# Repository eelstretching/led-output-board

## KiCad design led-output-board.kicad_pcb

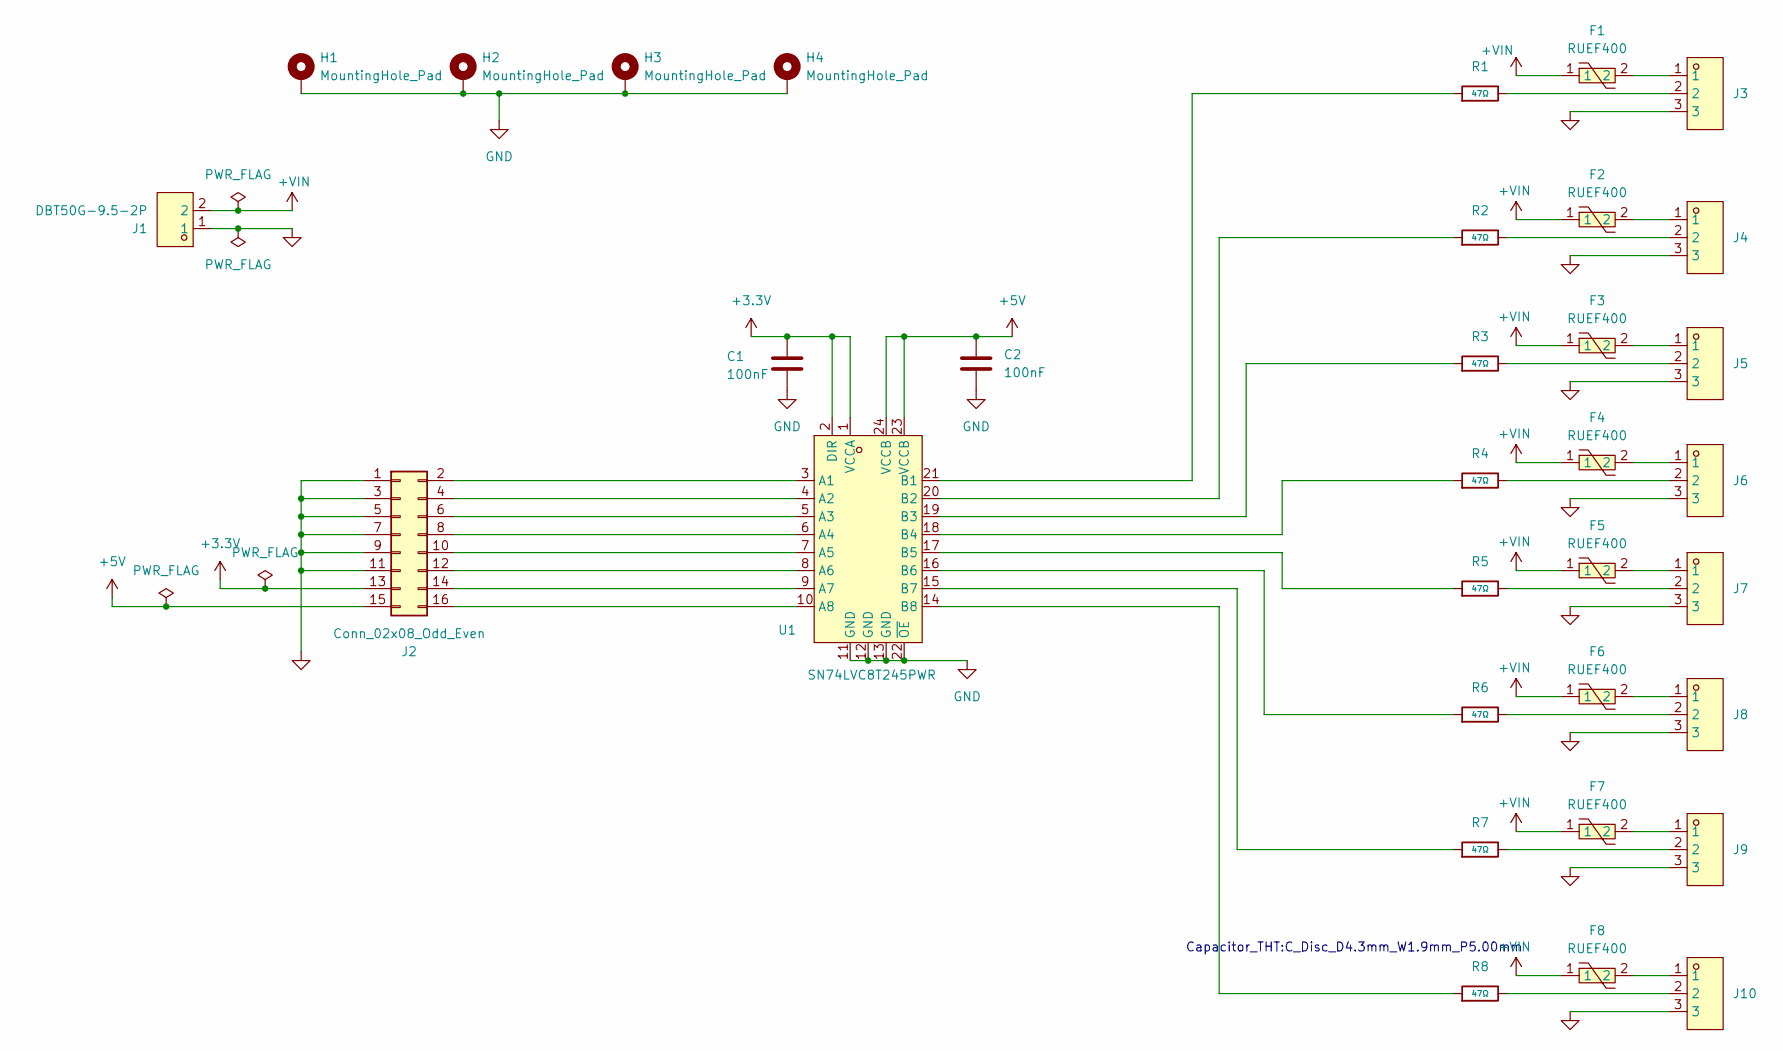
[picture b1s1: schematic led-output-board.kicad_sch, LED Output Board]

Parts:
C1, C2: 100nF; C_Disc_D4.3mm_W1.9mm_P5.00mm
F1, F2, F3, F4, F5, F6, F7, F8: RUEF400; FUSE-TH_L14.0-W3.0-P5.08-D0.6; MPN RUEF400; LCSC Part C2760163
H1, H2, H3, H4: MountingHole_Pad; MountingHole_3.2mm_M3_Pad
J1: DBT50G-9.5-2P; CONN-TH_2P-P9.50_DBT50G-9.5-2P
J2: Conn_02x08_Odd_Even; IDC-Header_2x08_P2.54mm_Vertical
J3, J4, J5, J6, J7, J8, J9, J10: DB301V-3.5-3P-GN; CONN-TH_DB301V-3.5-3P-GN; LCSC Part C695630
R1, R2, R3, R4, R5, R6, R7, R8: 47Ω; R_Axial_DIN0204_L3.6mm_D1.6mm_P2.54mm_Vertical; Overload Voltage (Max) 50V; Tolerance ±1%; Part 0402WGF470JTCE
U1: SN74LVC8T245PWR; TSSOP-24_L7.8-W4.4-P0.65-LS6.4-BL; LCSC Part C27643

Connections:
+3.3V: C1.1, J2.13, U1.1 (VCCA), U1.2 (DIR)
+5V: C2.1, J2.15, U1.23 (VCCB), U1.24 (VCCB)
+VIN: F1.1, F2.1, F3.1, F4.1, F5.1, F6.1, F7.1, F8.1, J1.2
GND: C1.2, C2.2, H1.1 (1_1), H2.1 (1_1), H3.1 (1_1), H4.1 (1_1), J1.1, J2.1, J2.3, J2.5, J2.7, J2.9, J2.11, J3.3, J4.3, J5.3, J6.3, J7.3, J8.3, J9.3, J10.3, U1.11 (GND), U1.12 (GND), U1.13 (GND), U1.22 (~OE)
unnamed: F1.2, J3.1
unnamed: F2.2, J4.1
unnamed: F3.2, J5.1
unnamed: F4.2, J6.1
unnamed: F5.2, J7.1
unnamed: F6.2, J8.1
unnamed: F7.2, J9.1
unnamed: F8.2, J10.1
unnamed: J2.2, U1.3 (A1)
unnamed: J2.4, U1.4 (A2)
unnamed: J2.6, U1.5 (A3)
unnamed: J2.8, U1.6 (A4)
unnamed: J2.10, U1.7 (A5)
unnamed: J2.12, U1.8 (A6)
unnamed: J2.14, U1.9 (A7)
unnamed: J2.16, U1.10 (A8)
unnamed: J3.2, R1.2
unnamed: J4.2, R2.2
unnamed: J5.2, R3.2
unnamed: J6.2, R4.2
unnamed: J7.2, R5.2
unnamed: J8.2, R6.2
unnamed: J9.2, R7.2
unnamed: J10.2, R8.2
unnamed: R1.1, U1.21 (B1)
unnamed: R2.1, U1.20 (B2)
unnamed: R3.1, U1.19 (B3)
unnamed: R4.1, U1.18 (B4)
unnamed: R5.1, U1.17 (B5)
unnamed: R6.1, U1.16 (B6)
unnamed: R7.1, U1.15 (B7)
unnamed: R8.1, U1.14 (B8)

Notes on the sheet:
Capacitor_THT:C_Disc_D4.3mm_W1.9mm_P5.00mm

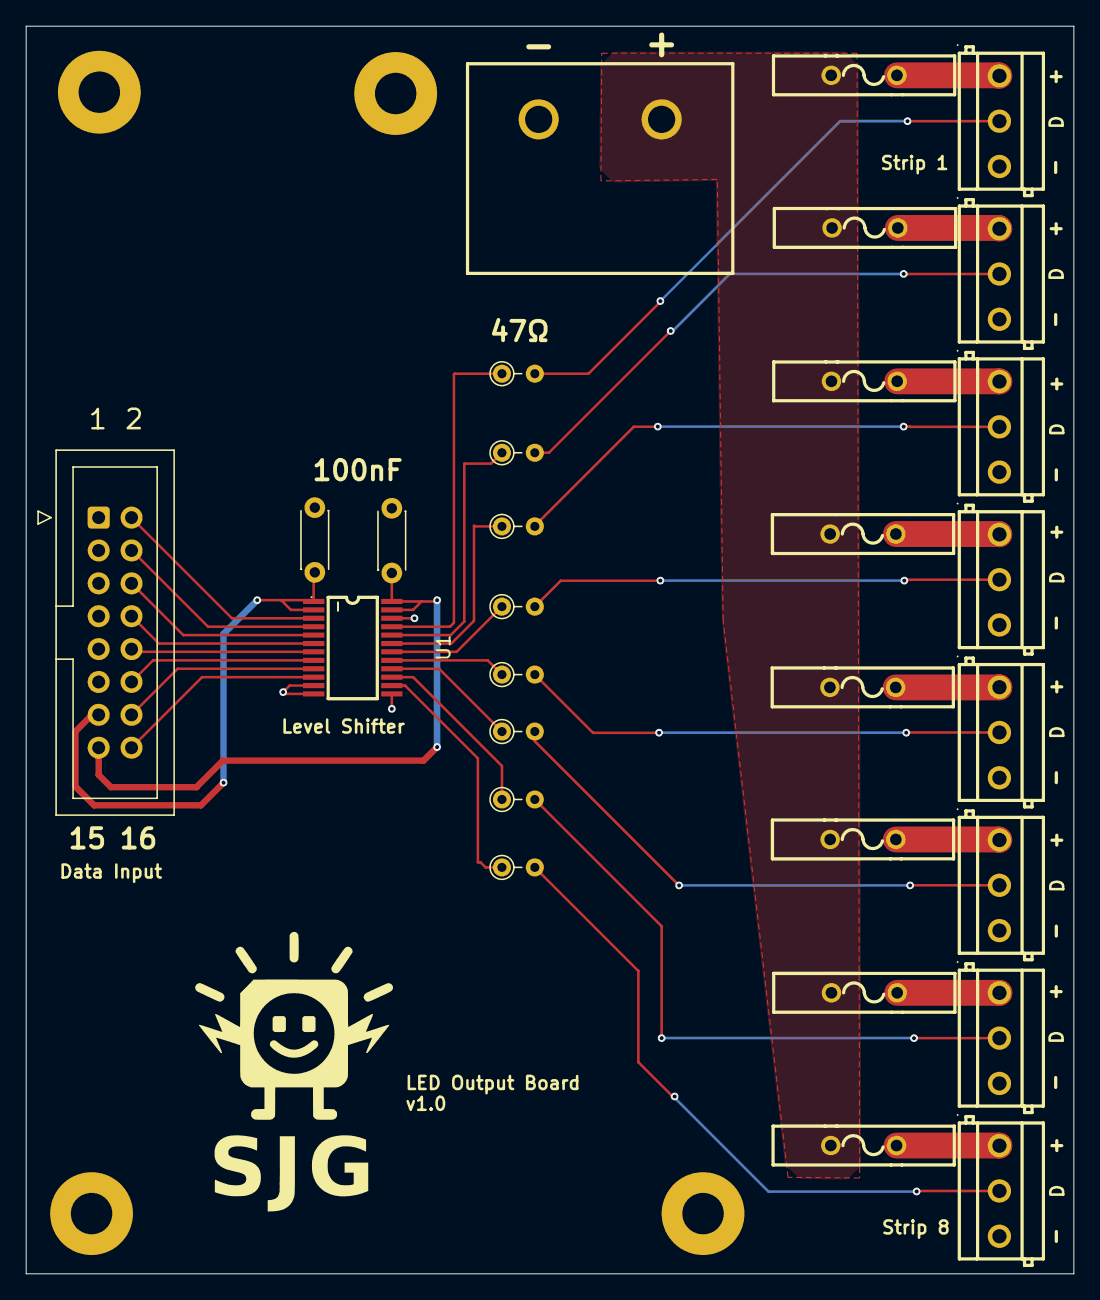
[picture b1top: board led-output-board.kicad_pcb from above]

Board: 2 copper layers, 80.9 x 96.4 mm, 33 parts (0 on the bottom side), 36 nets.
